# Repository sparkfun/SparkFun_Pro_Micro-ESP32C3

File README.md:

SparkFun Pro Micro ESP32-C3
========================================

[*SparkFun Pro Micro ESP32-C3 (DEV-23484)*](https://www.sparkfun.com/products/23484)

Don't be fooled by its miniature size; the SparkFun Pro Micro ESP32-C3 packs a punch. This micro marvel crams the powerful ESP32-C3, a single-core RISC-V powerhouse with 400KB of SRAM, into a compact 1.3in. x 0.7in. board. Clocking in at 160MHz, it's ready to tackle your projects quickly and efficiently.

Forget wires and soldering headaches – the Pro Micro ESP32-C3 embraces the simplicity of the Qwiic connector. Just plug and play any Qwiic sensor and watch your projects come alive with environmental data, motion detection, or whatever your imagination conjures. And stay connected, wherever you are, with built-in WiFi and Bluetooth® 5 (LE).

But the Pro Micro ESP32-C3 isn't just about small talk. Its 22 programmable GPIOs, accessible through handy castellated headers, unlock a multitude of possibilities. From tinkering with LEDs and servos to crafting intricate sensor networks, this tiny titan has the muscle to handle it all. And thanks to support for a range of protocols like ADC, SPI, UART, and I<sup>2</sup>C, the creative toolbox keeps expanding.

The Pro Micro ESP32-C3 taps into the power of Espressif's open-source ESP-IDF, a robust ecosystem brimming with libraries, tools, and a supportive community. Plus, you can leverage the familiar Arduino IDE for a smooth development experience.

So whether you're building a wearable masterpiece, a chatty IoT gadget, or a robotic friend, the SparkFun Pro Micro ESP32-C3 is your pint-sized partner in innovation. Grab one today and let your small-scale dreams take flight!

Repository Contents
-------------------

* **/Documentation** - Data sheets, additional product information
* **/Hardware** - Eagle design files (.brd, .sch)
* **/Production** - Production panel files (.brd)

Documentation
--------------
* **[Hookup Guide](https://docs.sparkfun.com/SparkFun_Pro_Micro-ESP32C3)** - Basic hookup guide for the SparkFun Pro Micro ESP32-C3

License Information
-------------------

This product is _**open source**_! 

Please review the LICENSE.md file for license information. 

If you have any questions or concerns on licensing, please contact technical support on our [SparkFun forums](https://forum.sparkfun.com/viewforum.php?f=152).

Distributed as-is; no warranty is given.

- Your friends at SparkFun.

_<COLLABORATION CREDIT>_

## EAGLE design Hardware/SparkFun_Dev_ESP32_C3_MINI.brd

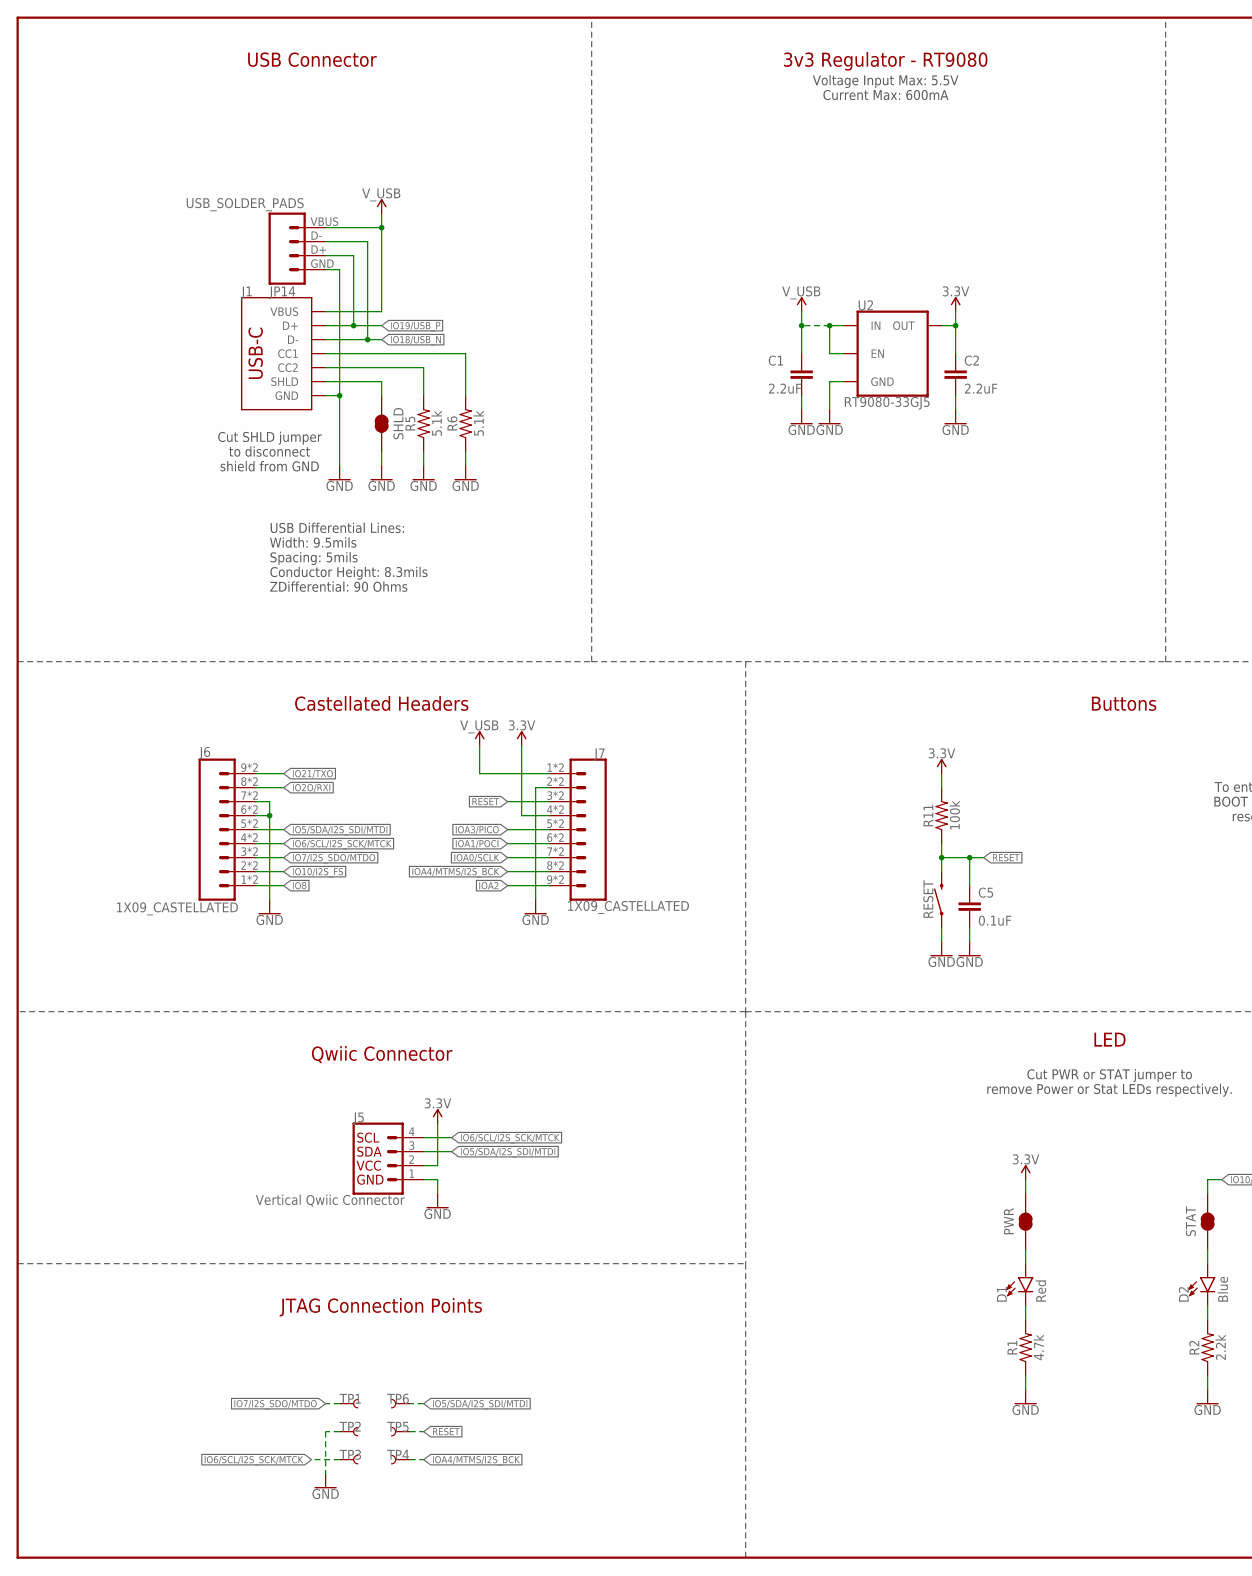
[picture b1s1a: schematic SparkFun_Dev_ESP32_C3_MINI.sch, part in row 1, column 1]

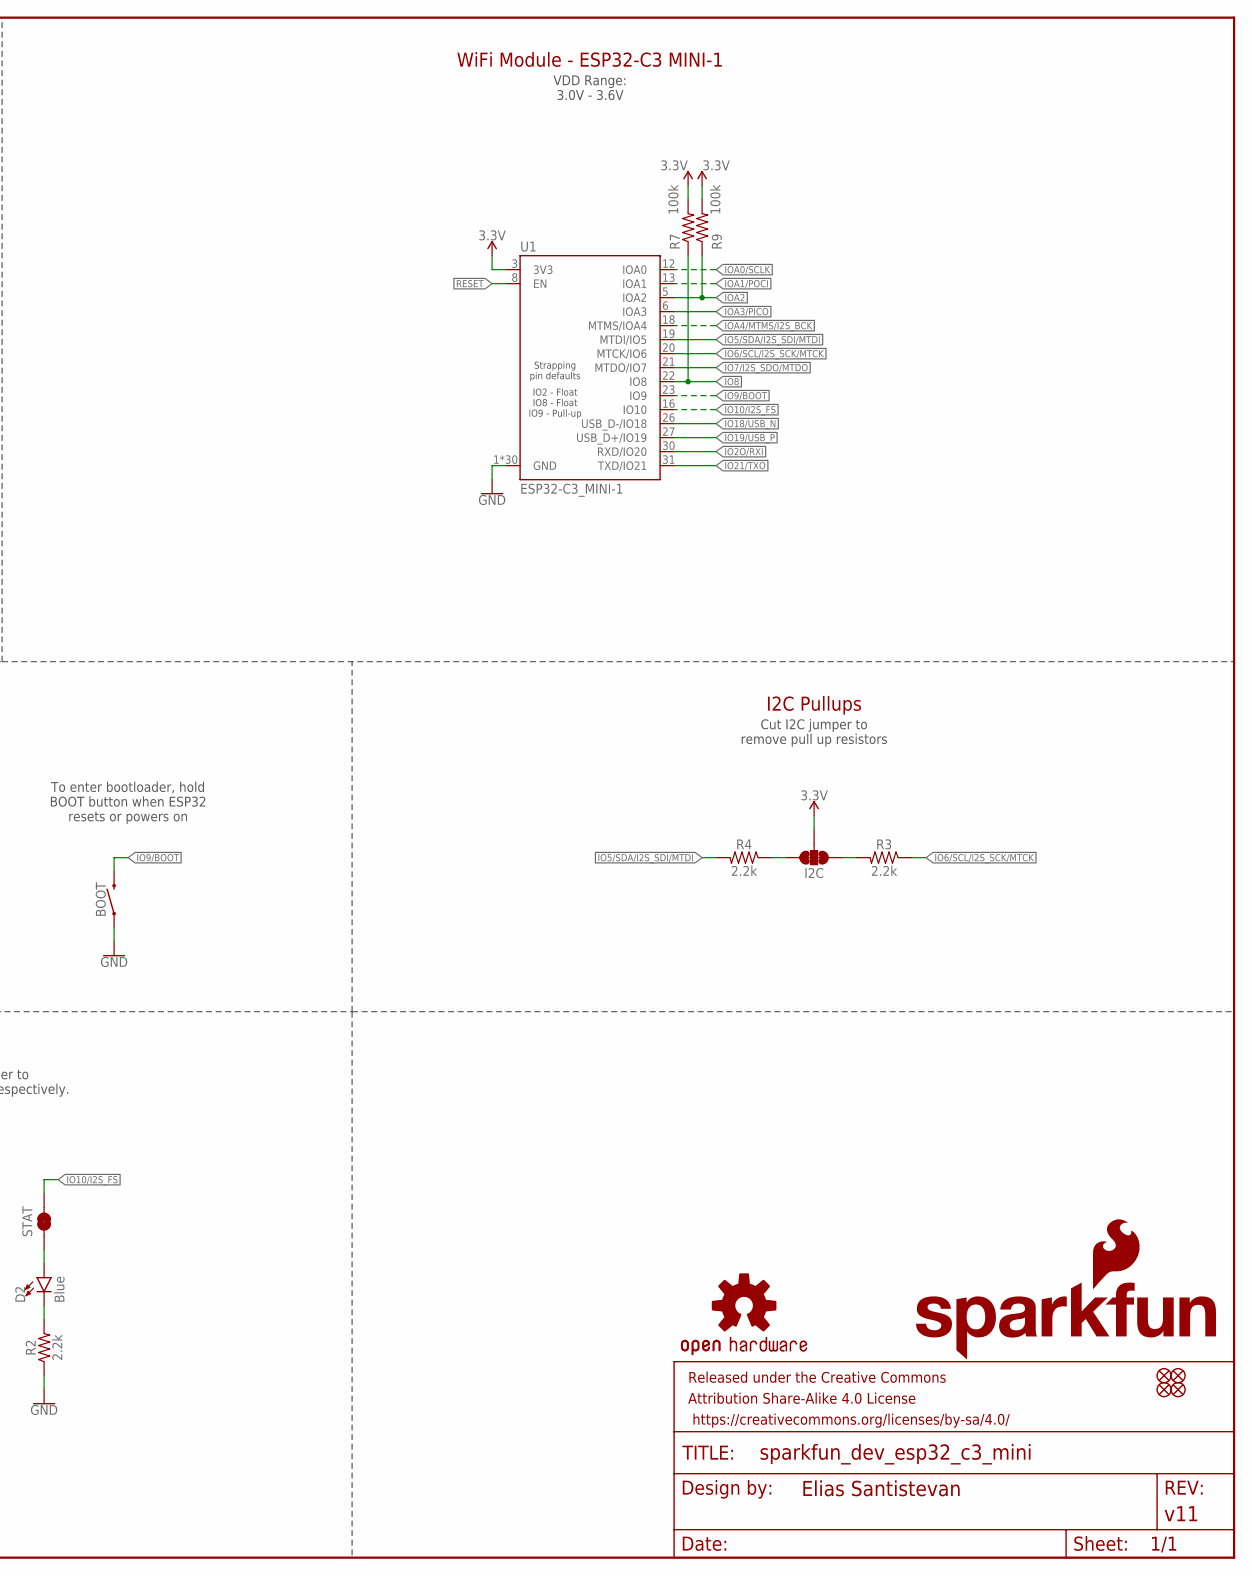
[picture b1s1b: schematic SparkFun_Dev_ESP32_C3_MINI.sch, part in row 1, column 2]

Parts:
BOOT: MOMENTARY-SWITCH-SPST-SMD-4.6X2.8MM; TACTILE_SWITCH_SMD_4.6X2.8MM
C1, C2: 2.2uF; 0402-TIGHT
C5: 0.1uF; 0402-TIGHT
D1: Red; LED-0603
D2: Blue; LED-0603
FD1, FD2, FD3, FD4: FIDUCIALUFIDUCIAL; FIDUCIAL-MICRO
FRAME2: FRAME-LEDGER; CREATIVE_COMMONS
I2C: JUMPER-SMT_3_2-NC_TRACE_SILK; SMT-JUMPER_3_2-NC_TRACE_SILK
J1: USB Female Type C Connector; USB-C-16P_4LAYER-PADS
J5: Vertical Qwiic Connector; JST04_1MM_VERT
J6, J7: 1X09_CASTELLATED
JP14: USB_SOLDER_PADS; USB-SOLDER-PADS
LOGO1: SFE_LOGO_NAME_FLAMEBLANK; BLANK
LOGO3: OSHW-LOGOS; OSHW-LOGO-S
PWR: JUMPER-SMT_2_NC_TRACE_SILK; SMT-JUMPER_2_NC_TRACE_SILK
R1: 4.7k; 0402-TIGHT
R2, R3, R4: 2.2k; 0402-TIGHT
R5, R6: 5.1k; 0402-TIGHT
R7, R9, R11: 100k; 0402-TIGHT
RESET: MOMENTARY-SWITCH-SPST-SMD-4.6X2.8MM; TACTILE_SWITCH_SMD_4.6X2.8MM
SHLD: JUMPER-SMT_2_NC_TRACE_SILK; SMT-JUMPER_2_NC_TRACE_SILK
STAT: JUMPER-SMT_2_NC_TRACE_SILK; SMT-JUMPER_2_NC_TRACE_SILK
TP1, TP2, TP3, TP4, TP5, TP6: TEST-POINT3X5; PAD.03X.05
U1: ESP32-C3_MINI-1; ESP32-C3-MINI-1
U2: RT9080-33GJ5; SOT23-5

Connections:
3.3V: C2.1, I2C.2, J5.2, J7.4, J7.4B (4), PWR.2, R7.2, R9.2, R11.2, U1.3 (3V3), U2.5 (OUT)
!RESET!: C5.1, J7.3, J7.3B (3), R11.1, RESET.3 (2), RESET.4 (2), TP5.1, U1.8 (EN)
GND: BOOT.1, BOOT.2 (1), C1.2, C2.2, C5.2, J1.GND, J1.GND2 (GND), J5.1, J6.6, J6.6B (6), J6.7, J6.7B (7), J7.2, J7.2B (2), JP14.GND (4), R1.1, R2.1, R5.1, R6.1, RESET.1, RESET.2 (1), SHLD.2, TP2.1, U1.1 (GND), U1.2 (GND), U1.11 (GND), U1.14 (GND), U1.36 (GND), U1.37 (GND), U1.38 (GND), U1.39 (GND), U1.40 (GND), U1.41 (GND), U1.42 (GND), U1.43 (GND), U1.44 (GND), U1.45 (GND), U1.46 (GND), U1.47 (GND), U1.48 (GND), U1.49.1 (GND), U1.49.2 (GND), U1.49.3 (GND), U1.49.4 (GND), U1.49.5 (GND), U1.49.6 (GND), U1.49.7 (GND), U1.49.8 (GND), U1.49.9 (GND), U1.50 (GND), U1.51 (GND), U1.52 (GND), U1.53 (GND), U2.2 (GND)
IO2O/RXI: J6.8, J6.8B (8), U1.30 (RXD/IO20)
IO5/SDA/I2S_SDI/MTDI: J5.3, J6.5, J6.5B (5), R4.2, TP6.1, U1.19 (MTDI/IO5)
IO6/SCL/I2S_SCK/MTCK: J5.4, J6.4, J6.4B (4), R3.1, TP3.1, U1.20 (MTCK/IO6)
IO7/I2S_SDO/MTDO: J6.3, J6.3B (3), TP1.1, U1.21 (MTDO/IO7)
IO8: J6.1, J6.1B (1), R7.1, U1.22 (IO8)
IO9/BOOT: BOOT.3 (2), BOOT.4 (2), U1.23 (IO9)
IO10/I2S_FS: J6.2, J6.2B (2), STAT.2, U1.16 (IO10)
IO18/USB_N: J1.A7 (D-), J1.B7 (D-), JP14.D- (2), U1.26 (USB_D-/IO18)
IO19/USB_P: J1.A6 (D+), J1.B6 (D+), JP14.D+ (3), U1.27 (USB_D+/IO19)
IO21/TXO: J6.9, J6.9B (9), U1.31 (TXD/IO21)
IOA0/SCLK: J7.7, J7.7B (7), U1.12 (IOA0)
IOA1/POCI: J7.6, J7.6B (6), U1.13 (IOA1)
IOA2: J7.9, J7.9B (9), R9.1, U1.5 (IOA2)
IOA3/PICO: J7.5, J7.5B (5), U1.6 (IOA3)
IOA4/MTMS/I2S_BCK: J7.8, J7.8B (8), TP4.1, U1.18 (MTMS/IOA4)
unnamed: D1.C, R1.2
unnamed: D1.A, PWR.1
unnamed: D2.C, R2.2
unnamed: I2C.3, R3.2
unnamed: I2C.1, R4.1
unnamed: J1.B5 (CC2), R5.2
unnamed: J1.A5 (CC1), R6.2
unnamed: D2.A, STAT.1
SHLD: J1.SHLD1 (SHLD), J1.SHLD2 (SHLD), J1.SHLD3 (SHLD), J1.SHLD4 (SHLD), SHLD.1
V_USB: C1.1, J1.VBUS1 (VBUS), J1.VBUS2 (VBUS), J7.1, J7.1B (1), JP14.VBUS (1), U2.1 (IN), U2.3 (EN)

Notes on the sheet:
USB Connector
3v3 Regulator - RT9080
Qwiic Connector
Castellated Headers
LED
Buttons
I2C Pullups
WiFi Module - ESP32-C3 MINI-1
VDD Range: 3.0V - 3.6V
Cut I2C jumper to remove pull up resistors
Cut PWR or STAT jumper to remove Power or Stat LEDs respectively.
Voltage Input Max: 5.5V Current Max: 600mA
To enter bootloader, hold BOOT button when ESP32 resets or powers on
Cut SHLD jumper to disconnect shield from GND
JTAG Connection Points
USB Differential Lines: Width: 9.5mils Spacing: 5mils Conductor Height: 8.3mils ZDifferential: 90 Ohms

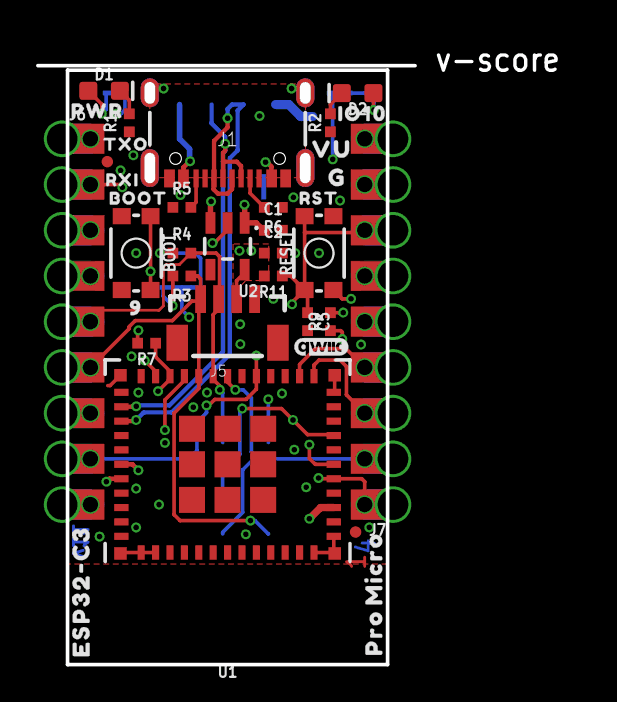
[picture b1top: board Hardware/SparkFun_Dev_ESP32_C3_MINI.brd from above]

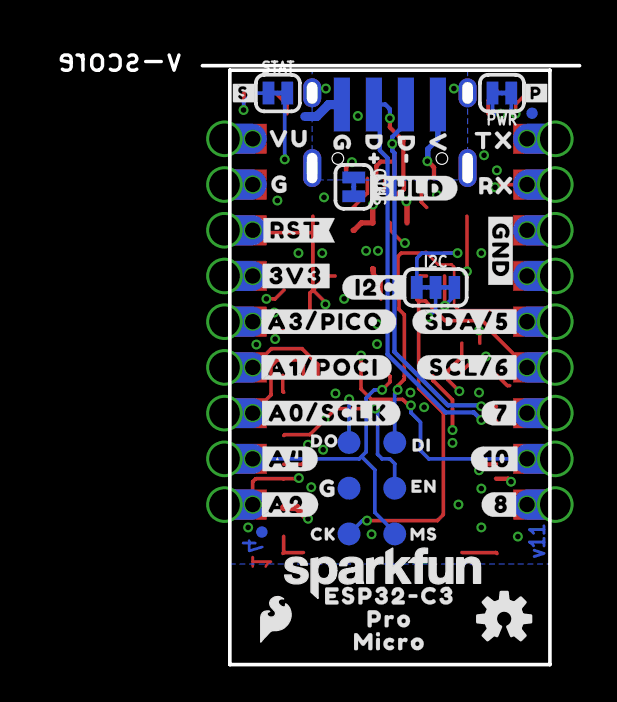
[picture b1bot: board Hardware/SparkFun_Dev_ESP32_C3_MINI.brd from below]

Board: 4 copper layers, 29.7 x 34.4 mm, 90 parts (50 on the bottom side), 28 nets.

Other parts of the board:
U$1, U$31, U$33, U$39: G36
U$2: IO1044
U$3: 93
U$4: #3V3#0
U$5: RST41
U$6: #I2C#947
U$7: #P#49
U$8: #S#51
U$9: #RST#945
U$10, U$51: VU35
U$11: #SHLD#946
U$12: #8#50
U$13: #A1#POCI#50
U$14: #A0#SCLK#50
U$15: #A4#50
U$16: #A2#50
U$17: TX40
U$18: SFE_LOGO_NAME_.1
U$20: #7#50
U$21: #10#50
U$22: #GND#4
U$23: CK39
U$24: ORDERING_INSTRUCTIONS
U$25: D#33
U$26: D#34
U$27: DI36
U$28: DO35
U$29: EN37
U$30: MS38
U$32: V35
U$34, U$45: ESP32#C32
U$35, U$46: PRO0
U$36, U$47: MICRO1
U$37: RX39
U$40: #A3#PICO#45
U$41: BOOT15
U$42: RXI39
U$43: TXO40
U$44: #SDA#5#10952
U$48: SFE_LOGO_FLAME_.1
U$49: PWR945
U$50: QWIIC_3MM
U$53: #SCL#6#10952

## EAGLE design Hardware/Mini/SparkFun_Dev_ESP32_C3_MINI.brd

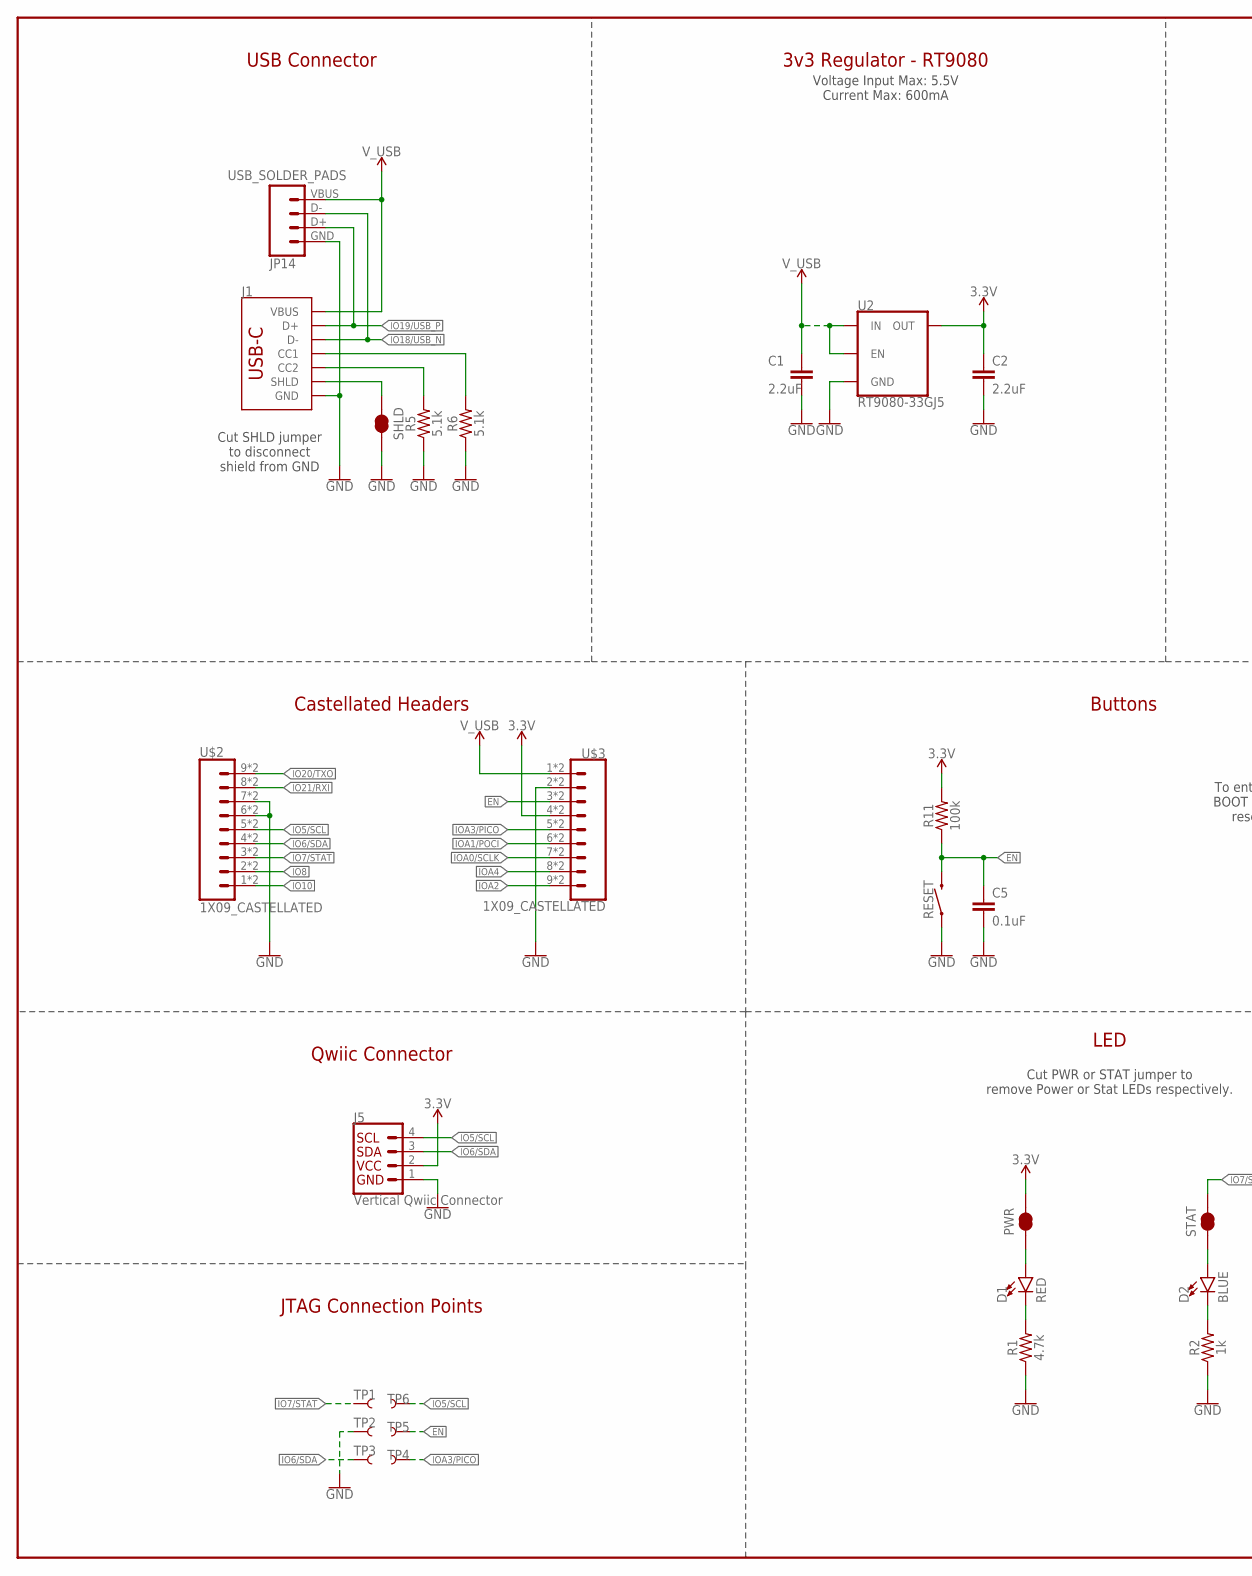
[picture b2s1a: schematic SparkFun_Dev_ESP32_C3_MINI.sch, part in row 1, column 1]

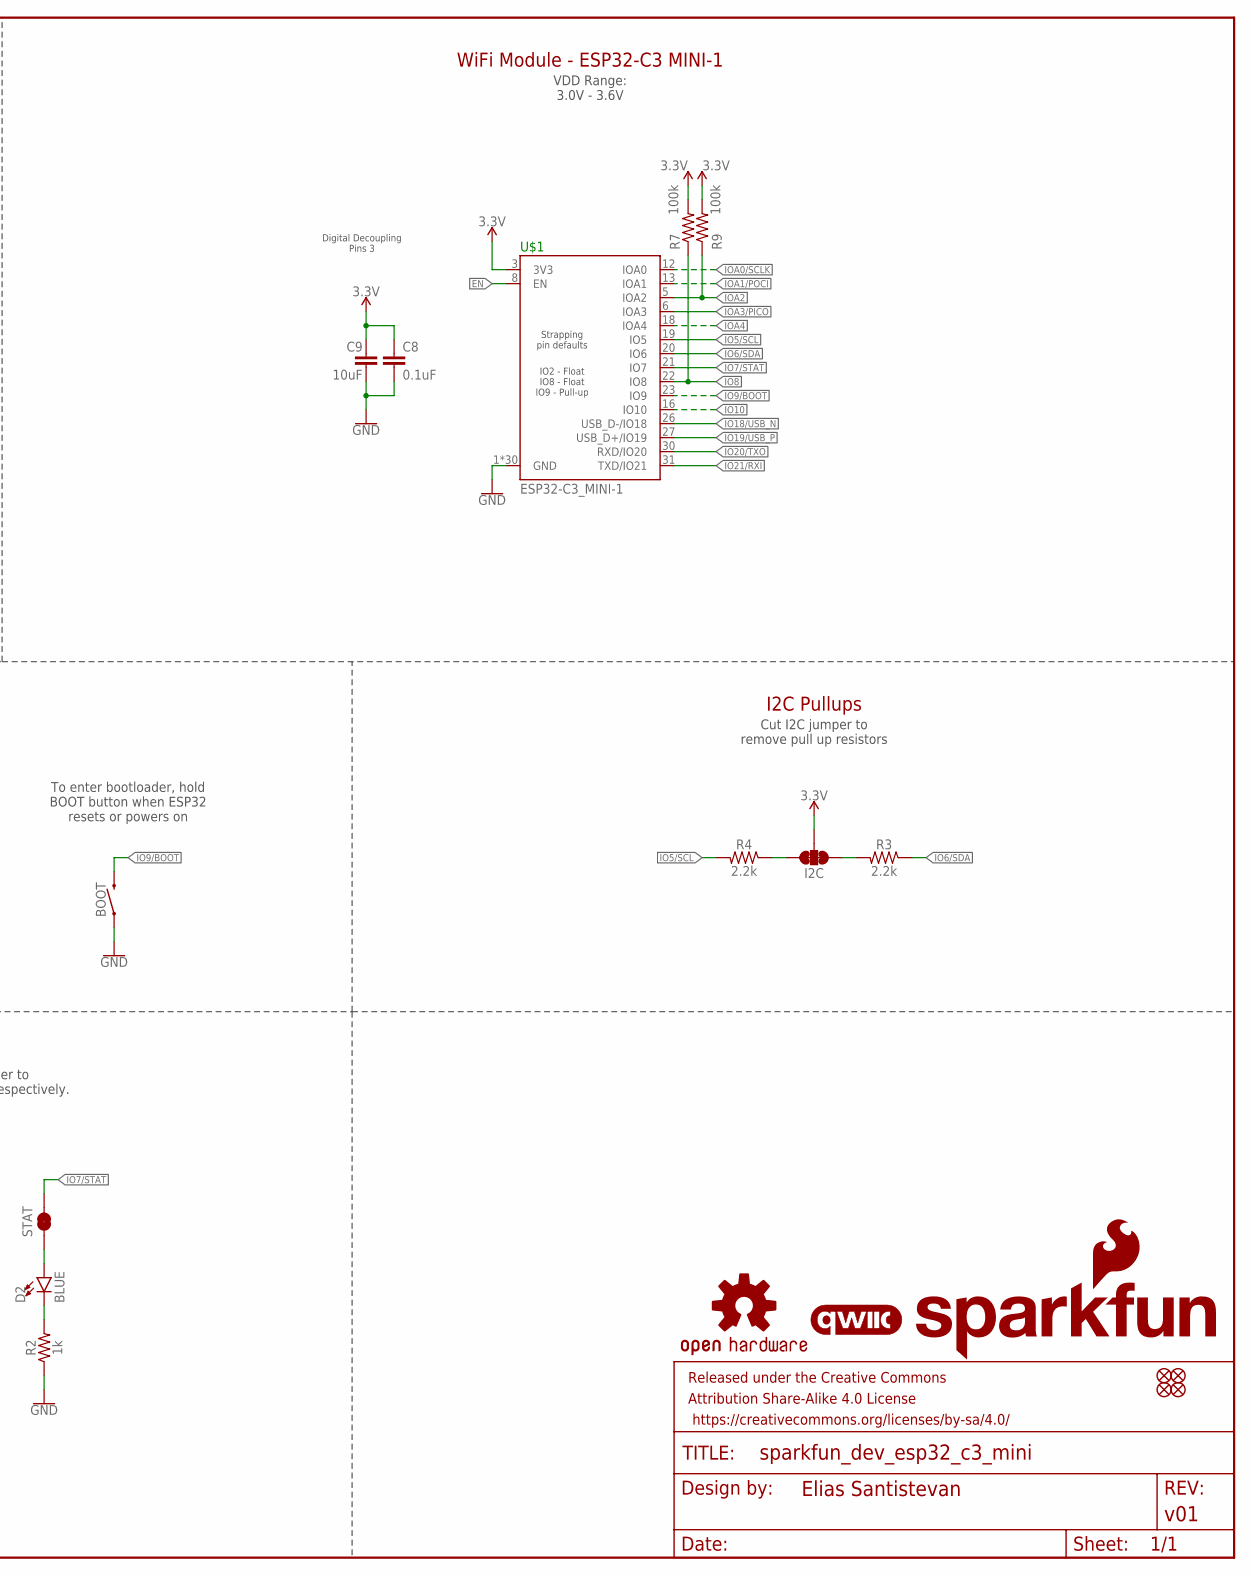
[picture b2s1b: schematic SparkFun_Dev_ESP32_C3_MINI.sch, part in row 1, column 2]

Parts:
BOOT: MOMENTARY-SWITCH-SPST-SMD-4.6X2.8MM; TACTILE_SWITCH_SMD_4.6X2.8MM
C1, C2: 2.2uF; 0402-TIGHT
C5, C8: 0.1uF; 0402-TIGHT
C9: 10uF; 0402-TIGHT
D1: RED; LED-0603
D2: BLUE; LED-0603
FD1, FD2, FD3, FD4: FIDUCIALUFIDUCIAL; FIDUCIAL-MICRO
FRAME2: FRAME-LEDGER; CREATIVE_COMMONS
I2C: JUMPER-SMT_3_2-NC_TRACE_SILK; SMT-JUMPER_3_2-NC_TRACE_SILK
J1: USB Female Type C Connector; USB-C-16P_4LAYER-PADS
J5: Vertical Qwiic Connector; JST04_1MM_VERT
JP14: USB_SOLDER_PADS; USB-SOLDER-PADS
LOGO1: SFE_LOGO_NAME_FLAMEBLANK; BLANK
LOGO2: QWIIC_LOGO_3MM; QWIIC_3MM
LOGO3: OSHW-LOGOS; OSHW-LOGO-S
PWR: JUMPER-SMT_2_NC_TRACE_SILK; SMT-JUMPER_2_NC_TRACE_SILK
R1: 4.7k; 0402-TIGHT
R2: 1k; 0402-TIGHT
R3, R4: 2.2k; 0402-TIGHT
R5, R6: 5.1k; 0402-TIGHT
R7, R9, R11: 100k; 0402-TIGHT
RESET: MOMENTARY-SWITCH-SPST-SMD-4.6X2.8MM; TACTILE_SWITCH_SMD_4.6X2.8MM
SHLD: JUMPER-SMT_2_NC_TRACE_SILK; SMT-JUMPER_2_NC_TRACE_SILK
STAT: JUMPER-SMT_2_NC_TRACE_SILK; SMT-JUMPER_2_NC_TRACE_SILK
TP1, TP2, TP3, TP4, TP5, TP6: TEST-POINT3X5; PAD.03X.05
U2: RT9080-33GJ5; SOT23-5
U$1: ESP32-C3_MINI-1; ESP32-C3-MINI-1
U$2, U$3: 1X09_CASTELLATED

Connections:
3.3V: C2.1, C8.1, C9.1, I2C.2, J5.2, PWR.2, R7.2, R9.2, R11.2, U2.5 (OUT), U$1.3 (3V3), U$3.4, U$3.4B (4)
EN: C5.1, R11.1, RESET.3 (2), RESET.4 (2), TP5.1, U$1.8 (EN), U$3.3, U$3.3B (3)
GND: BOOT.1, BOOT.2 (1), C1.2, C2.2, C5.2, C8.2, C9.2, J1.GND, J1.GND2 (GND), J5.1, JP14.GND (4), R1.1, R2.1, R5.1, R6.1, RESET.1, RESET.2 (1), SHLD.2, TP2.1, U2.2 (GND), U$1.1 (GND), U$1.2 (GND), U$1.11 (GND), U$1.14 (GND), U$1.36 (GND), U$1.37 (GND), U$1.38 (GND), U$1.39 (GND), U$1.40 (GND), U$1.41 (GND), U$1.42 (GND), U$1.43 (GND), U$1.44 (GND), U$1.45 (GND), U$1.46 (GND), U$1.47 (GND), U$1.48 (GND), U$1.49.1 (GND), U$1.49.2 (GND), U$1.49.3 (GND), U$1.49.4 (GND), U$1.49.5 (GND), U$1.49.6 (GND), U$1.49.7 (GND), U$1.49.8 (GND), U$1.49.9 (GND), U$1.50 (GND), U$1.51 (GND), U$1.52 (GND), U$1.53 (GND), U$2.6, U$2.6B (6), U$2.7, U$2.7B (7), U$3.2, U$3.2B (2)
IO5/SCL: J5.4, R4.2, TP6.1, U$1.19 (IO5), U$2.5, U$2.5B (5)
IO6/SDA: J5.3, R3.1, TP3.1, U$1.20 (IO6), U$2.4, U$2.4B (4)
IO7/STAT: STAT.2, TP1.1, U$1.21 (IO7), U$2.3, U$2.3B (3)
IO8: R7.1, U$1.22 (IO8), U$2.2, U$2.2B (2)
IO9/BOOT: BOOT.3 (2), BOOT.4 (2), U$1.23 (IO9)
IO10: U$1.16 (IO10), U$2.1, U$2.1B (1)
IO18/USB_N: J1.A7 (D-), J1.B7 (D-), JP14.D- (2), U$1.26 (USB_D-/IO18)
IO19/USB_P: J1.A6 (D+), J1.B6 (D+), JP14.D+ (3), U$1.27 (USB_D+/IO19)
IO20/TXO: U$1.30 (RXD/IO20), U$2.9, U$2.9B (9)
IO21/RXI: U$1.31 (TXD/IO21), U$2.8, U$2.8B (8)
IOA0/SCLK: U$1.12 (IOA0), U$3.7, U$3.7B (7)
IOA1/POCI: U$1.13 (IOA1), U$3.6, U$3.6B (6)
IOA2: R9.1, U$1.5 (IOA2), U$3.9, U$3.9B (9)
IOA3/PICO: TP4.1, U$1.6 (IOA3), U$3.5, U$3.5B (5)
IOA4: U$1.18 (IOA4), U$3.8, U$3.8B (8)
unnamed: D1.C, R1.2
unnamed: D1.A, PWR.1
unnamed: D2.C, R2.2
unnamed: I2C.3, R3.2
unnamed: I2C.1, R4.1
unnamed: J1.B5 (CC2), R5.2
unnamed: J1.A5 (CC1), R6.2
unnamed: D2.A, STAT.1
SHLD: J1.SHLD1 (SHLD), J1.SHLD2 (SHLD), J1.SHLD3 (SHLD), J1.SHLD4 (SHLD), SHLD.1
V_USB: C1.1, J1.VBUS1 (VBUS), J1.VBUS2 (VBUS), JP14.VBUS (1), U2.1 (IN), U2.3 (EN), U$3.1, U$3.1B (1)

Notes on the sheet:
USB Connector
3v3 Regulator - RT9080
Qwiic Connector
Castellated Headers
LED
Buttons
I2C Pullups
WiFi Module - ESP32-C3 MINI-1
VDD Range: 3.0V - 3.6V
Cut I2C jumper to remove pull up resistors
Cut PWR or STAT jumper to remove Power or Stat LEDs respectively.
Voltage Input Max: 5.5V Current Max: 600mA
To enter bootloader, hold BOOT button when ESP32 resets or powers on
Cut SHLD jumper to disconnect shield from GND
Digital Decoupling Pins 3
JTAG Connection Points

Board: 4 copper layers, 44 parts (14 on the bottom side), 28 nets, no tracks yet.

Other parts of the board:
U$24: ORDERING_INSTRUCTIONS

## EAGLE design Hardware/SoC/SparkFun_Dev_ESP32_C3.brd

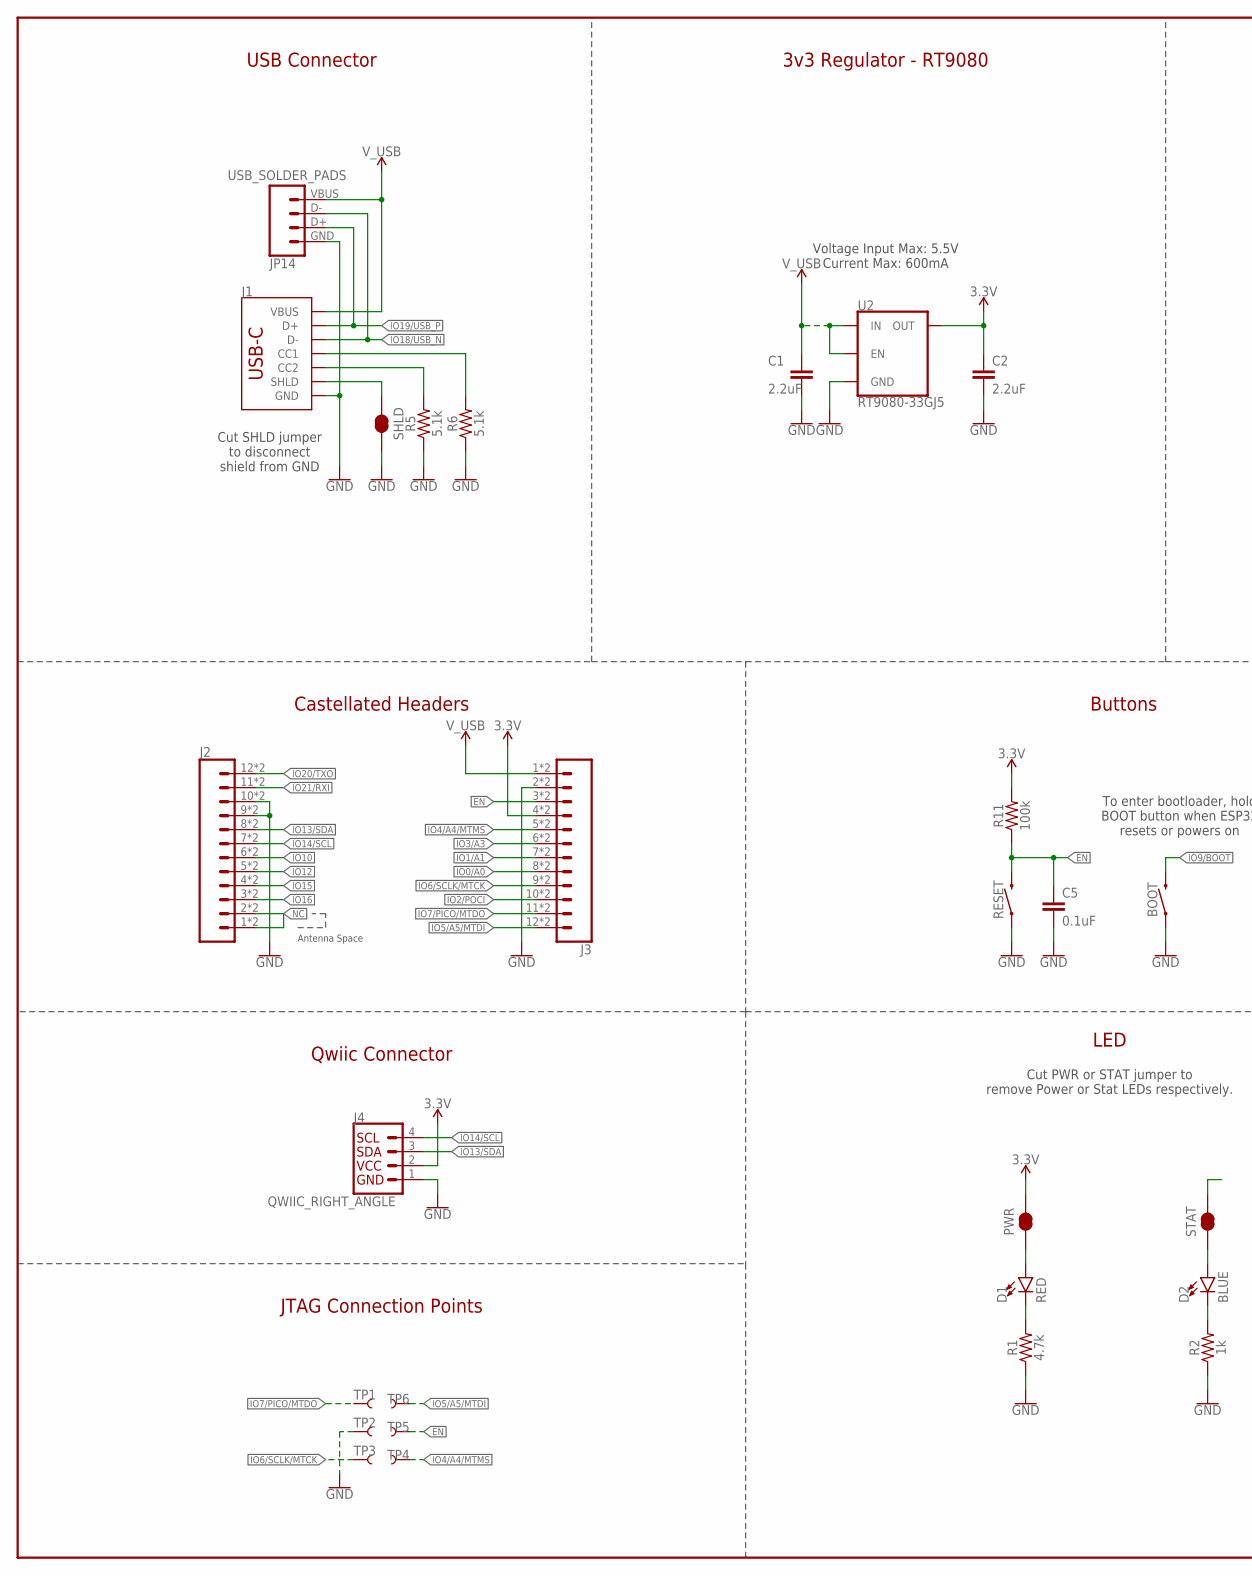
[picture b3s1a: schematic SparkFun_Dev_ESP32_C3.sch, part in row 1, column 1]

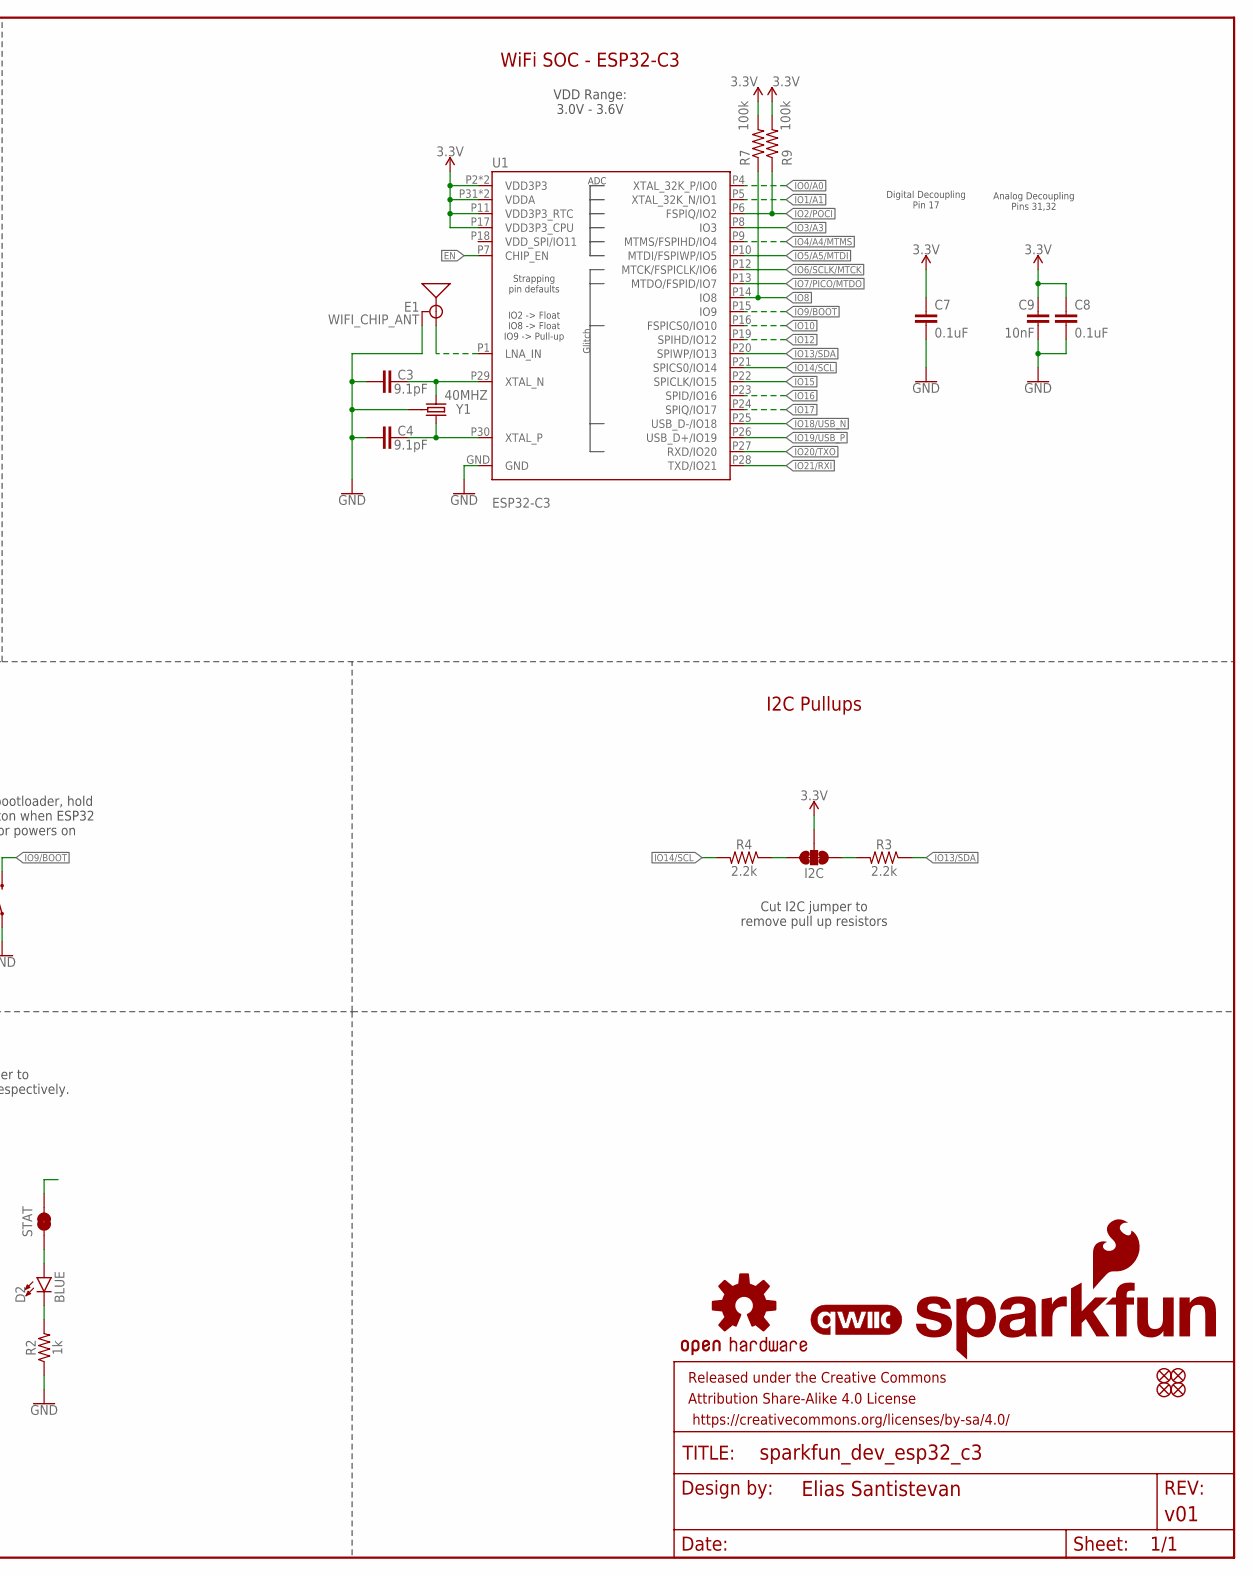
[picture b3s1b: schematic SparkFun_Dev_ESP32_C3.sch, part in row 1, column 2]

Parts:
BOOT: MOMENTARY-SWITCH-SPST-SMD-4.6X2.8MM; TACTILE_SWITCH_SMD_4.6X2.8MM
C1, C2: 2.2uF; 0402-TIGHT
C3, C4: 9.1pF; 0402-TIGHT
C5, C7, C8: 0.1uF; 0402-TIGHT
C9: 10nF; 0402-TIGHT
D1: RED; LED-0603
D2: BLUE; LED-0603
E1: WIFI_CHIP_ANT; CHIP_ANT_NO_COURTYARD
FD1, FD2, FD3, FD4: FIDUCIALUFIDUCIAL; FIDUCIAL-MICRO
FRAME2: FRAME-LEDGER; CREATIVE_COMMONS
I2C: JUMPER-SMT_3_2-NC_TRACE_SILK; SMT-JUMPER_3_2-NC_TRACE_SILK
J1: USB Female Type C Connector; USB-C-16P_4LAYER-PADS
J2, J3: CONN_12CASTELLATED; 1X12_CASTELLATED
J4: QWIIC_RIGHT_ANGLE; JST04_1MM_RA
JP14: USB_SOLDER_PADS; USB-SOLDER-PADS
LOGO1: SFE_LOGO_NAME_FLAMEBLANK; BLANK
LOGO2: QWIIC_LOGO_3MM; QWIIC_3MM
LOGO3: OSHW-LOGOS; OSHW-LOGO-S
PWR: JUMPER-SMT_2_NC_TRACE_SILK; SMT-JUMPER_2_NC_TRACE_SILK
R1: 4.7k; 0402-TIGHT
R2: 1k; 0402-TIGHT
R3, R4: 2.2k; 0402-TIGHT
R5, R6: 5.1k; 0402-TIGHT
R7, R9, R11: 100k; 0402-TIGHT
RESET: MOMENTARY-SWITCH-SPST-SMD-4.6X2.8MM; TACTILE_SWITCH_SMD_4.6X2.8MM
SHLD: JUMPER-SMT_2_NC_TRACE_SILK; SMT-JUMPER_2_NC_TRACE_SILK
STAT: JUMPER-SMT_2_NC_TRACE_SILK; SMT-JUMPER_2_NC_TRACE_SILK
TP1, TP2, TP3, TP4, TP5, TP6: TEST-POINT3X5; PAD.03X.05
U1: ESP32-C3; QFN32
U2: RT9080-33GJ5; SOT23-5
Y1: 40MHZ; CRYSTAL-SMD-2X2.5MM

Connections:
3.3V: C2.1, C7.1, C8.1, C9.1, I2C.2, J3.4, J3.4B (4), J4.2, PWR.2, R7.2, R9.2, R11.2, U1.P2 (VDD3P3), U1.P3 (VDD3P3), U1.P11 (VDD3P3_RTC), U1.P17 (VDD3P3_CPU), U1.P31 (VDDA), U1.P32 (VDDA), U2.5 (OUT)
ANT: E1.P1 (SIGNAL), U1.P1 (LNA_IN)
EN: C5.1, J3.3, J3.3B (3), R11.1, RESET.3 (2), RESET.4 (2), TP5.1, U1.P7 (CHIP_EN)
GND: BOOT.1, BOOT.2 (1), C1.2, C2.2, C3.1, C4.1, C5.2, C7.2, C8.2, C9.2, E1.P3 (GND), E1.P4 (GND), J1.GND, J1.GND2 (GND), J2.9, J2.9B (9), J2.10, J2.10B (10), J3.2, J3.2B (2), J4.1, JP14.GND (4), R1.1, R2.1, R5.1, R6.1, RESET.1, RESET.2 (1), SHLD.2, TP2.1, U1.GND, U2.2 (GND), Y1.P2 (GND), Y1.P4 (GND)
IO0/A0: J3.8, J3.8B (8), U1.P4 (XTAL_32K_P/IO0)
IO1/A1: J3.7, J3.7B (7), U1.P5 (XTAL_32K_N/IO1)
IO2/POCI: J3.10, J3.10B (10), R9.1, U1.P6 (FSPIQ/IO2)
IO3/A3: J3.6, J3.6B (6), U1.P8 (IO3)
IO4/A4/MTMS: J3.5, J3.5B (5), TP4.1, U1.P9 (MTMS/FSPIHD/IO4)
IO5/A5/MTDI: J3.12, J3.12B (12), TP6.1, U1.P10 (MTDI/FSPIWP/IO5)
IO6/SCLK/MTCK: J3.9, J3.9B (9), TP3.1, U1.P12 (MTCK/FSPICLK/IO6)
IO7/PICO/MTDO: J3.11, J3.11B (11), TP1.1, U1.P13 (MTDO/FSPID/IO7)
IO8: R7.1, U1.P14 (IO8)
IO9/BOOT: BOOT.3 (2), BOOT.4 (2), U1.P15 (IO9)
IO10: J2.6, J2.6B (6), U1.P16 (FSPICS0/IO10)
IO12: J2.5, J2.5B (5), U1.P19 (SPIHD/IO12)
IO13/SDA: J2.8, J2.8B (8), J4.3, R3.1, U1.P20 (SPIWP/IO13)
IO14/SCL: J2.7, J2.7B (7), J4.4, R4.2, U1.P21 (SPICS0/IO14)
IO15: J2.4, J2.4B (4), U1.P22 (SPICLK/IO15)
IO16: J2.3, J2.3B (3), U1.P23 (SPID/IO16)
IO17: U1.P24 (SPIQ/IO17)
IO18/USB_N: J1.A7 (D-), J1.B7 (D-), JP14.D- (2), U1.P25 (USB_D-/IO18)
IO19/USB_P: J1.A6 (D+), J1.B6 (D+), JP14.D+ (3), U1.P26 (USB_D+/IO19)
IO20/TXO: J2.12, J2.12B (12), U1.P27 (RXD/IO20)
IO21/RXI: J2.11, J2.11B (11), U1.P28 (TXD/IO21)
unnamed: D1.C, R1.2
unnamed: D1.A, PWR.1
unnamed: D2.C, R2.2
unnamed: I2C.3, R3.2
unnamed: I2C.1, R4.1
unnamed: J1.B5 (CC2), R5.2
unnamed: J1.A5 (CC1), R6.2
unnamed: C3.2, U1.P29 (XTAL_N), Y1.P1 (1)
unnamed: C4.2, U1.P30 (XTAL_P), Y1.P3 (2)
unnamed: D2.A, STAT.1
NC: J2.1, J2.1B (1), J2.2, J2.2B (2)
SHLD: J1.SHLD1 (SHLD), J1.SHLD2 (SHLD), J1.SHLD3 (SHLD), J1.SHLD4 (SHLD), SHLD.1
V_USB: C1.1, J1.VBUS1 (VBUS), J1.VBUS2 (VBUS), J3.1, J3.1B (1), JP14.VBUS (1), U2.1 (IN), U2.3 (EN)

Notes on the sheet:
USB Connector
3v3 Regulator - RT9080
Qwiic Connector
Castellated Headers
LED
Buttons
I2C Pullups
WiFi SOC - ESP32-C3
VDD Range: 3.0V - 3.6V
Cut I2C jumper to remove pull up resistors
Cut PWR or STAT jumper to remove Power or Stat LEDs respectively.
Voltage Input Max: 5.5V Current Max: 600mA
To enter bootloader, hold BOOT button when ESP32 resets or powers on
Cut SHLD jumper to disconnect shield from GND
Analog Decoupling Pins 31,32
Digital Decoupling Pin 17
JTAG Connection Points
Antenna Space

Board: 4 copper layers, 49 parts (14 on the bottom side), 37 nets, no tracks yet.

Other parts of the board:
U$24: ORDERING_INSTRUCTIONS

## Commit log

2023-08-14 Adds datasheet, adds footprint, starts design
2023-08-14 Shrinks design
2023-08-15 Adds crystal
2023-08-17 Adds more documentation, decoupling caps, antennas, rearranges schematic
2023-08-23 Adds new antenna, nets IO, removes STAT LED
2023-08-25 Moves towards Pro Micro form factor
2023-08-25 Moves the parts into position
2023-08-28 Fixes schematic
2023-08-28 More I/O netting from ESP32C3 to headers
2023-08-28 Adds JTAG header and corrects boot control configuration
2023-08-29 Moves any connections away from antenna
    * Finishes netting
2023-08-29 Updates thickness in ordering instructions
2023-08-31 Adds new datasheet
2023-08-31 Adds MINI module, creates new design with MINI module netted
2023-08-31 Moves some parts away as lost in thought
2023-08-31 Moves around some capacitors
2023-08-31 Adds PTH version
2023-09-01 Adds 9 pin connector to the MINI designs
2023-09-01 Fixes symbol for ESP32 SOC, adds a few more headers, adds new SOC PTH design
2023-09-01 Moves unused board files to "OLD"
2023-09-01 Some updates to layout
2023-09-01 Removes unnecessary documents, , moves boar daround
2023-09-01 Fixes net names that were blasted away
2023-09-01 Adds I2S nets, we'll see
2023-09-01 Adds new C3 module so that the device value is correct
    * Fixes testpoints
2023-09-01 Moves stat LED
2023-09-01 Paranoid upload
2023-09-05 Routes some nets
2023-09-05 Routes most signals (soppily)
2023-09-05 Routes EVEN MORE signals again, sloppily - no judgements
2023-09-05 Slight adjustment to TX
2023-09-06 Approves many many DRC errors generated by castellated leads
2023-09-06 Renames some nets for clarity, adds vias, cleans up ground pours, fixes air wires
2023-09-06 Adds most of the silk on the bottom side
2023-09-07 Adds more silk, removes some shield polygons on inner layers
    * Moves fiducials around
    * Swaps I2C lines at PTH header
2023-09-07 Adds measures
2023-09-07 Fixes UART lines at module
2023-09-07 Create README.md - Tempate
2023-09-08 Updates symbol to include correct JTAG interface
    * Updates nets to reflect JTAG correction, moves JTAG header and routes new JTAG connection
    * Updates silk for fix above
2023-09-11 Fixes castellation, adds removeable tab
    * Reduces minimum annular ring to 3mil
    * Adds silk to removeable tag
    * Changes "EN" silk to "RST"
2023-09-11 Adds PROD ID to ESP32 module
2023-09-11 Fixes various potential acid traps
2023-09-11 Adds a few vias, cams prototypes
2023-09-12 Shortens some nets, fixes some silk
2023-09-25 General outline of pins
2023-09-27 Initial checkin of docs
    NOT Complete
2023-09-28 Updating Repo Links
2023-10-18 renames board files
2023-10-19 Renames I2S pins
2023-10-25 Adds numerous aesthetic changes
    * Increases size of silk everywhere possible
    * Moves jumpers for LEDs to the corners underneath the respective LED.
2023-10-25 Adds more aesthetic changes
    * Note on previous commit: I2C labels were removed from silk
    * Fixes ground silk rectangle
    * rotates qwiic label
    * Shrinks VBUS polygon
    * Moves boot capacitor to other side of button
2023-10-25 Fixes DRC issues
    * Moves shield jumper away from VUSB via
2023-10-26 Moves version onto the PCB, and rolls version in schematic
2023-10-26 Fixes some acid traps, fixes some schematic odds and ends
2023-10-30 Updates to silk, reorders some pin names on ESP32 symbol
2023-10-30 Adds SparkFun logo
2023-10-30 Updates USB lines to get it even closer to 90 Ohms
2023-11-03 Adds gerbers for panel and note about castellated leads to ordering instructions
2023-12-06 Updates silk, and rolls to v11
2023-12-07 Small fix for ground pour
2023-12-07 Adds new panel
2023-12-07 Zips production files
2024-01-02 Updating hardware overview
2024-01-08 Update product link
2024-01-11 Updating example
2024-01-15 Fixing eagle file links and example stuff
2024-01-15 Fixing name and links
2024-01-15 Fixing Hardware Assembly
2024-01-15 Wording and format changes
2024-01-16 Finishing hardware assembly and fixing gif rotation
2024-01-16 Updating description per marketing
2024-02-01 Updated Schematic and EagleFiles
2024-02-02 Puts board files into their own folder
2024-02-02 Removes old hardware files, removes old libraries, replaces parts in local library with parts now in SparkFun Eagle libraries
2024-02-02 Renames boards.txt file to sparkfun_boards
2024-02-02 Adding instructions for esp32 board file installation
2024-02-05 Rename pins_arduino.h to pins_arduino.h
    Fixes camel case in variant folder name
2024-02-05 Deployed 9bf1e8d with MkDocs version: 1.5.3
2026-06-03 Deployed b302fbc with MkDocs version: 1.6.1

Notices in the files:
parts and their libraries:
SparkFun-Connectors: Licensing: Creative Commons ShareAlike 4.0 International - https://creativecommons.org/licenses/by-sa/4.0
SparkFun-Aesthetics: Released under the Creative Commons Attribution Share-Alike 4.0 License
SparkFun-Aesthetics: https://creativecommons.org/licenses/by-sa/4.0
